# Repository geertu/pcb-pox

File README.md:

# POX - Power-Opto Extension Board (KiCad PCB)

This is a small extension board to control operation of two development boards,
e.g. on your desk, or in a board farm.  It is mainly intended for use with
BCU/2 (https://github.com/geertu/pcb-bcu2), but it can be used with any
microcontroller or single-board computer that has a compatible I2C interface.

## Features

  - Controlled over I2C,
  - Two power control and measurement channels (3.3-14V, max. 3.2A),
  - Six opto-isolators for e.g. reset, wake-up, and keypress simulation.

## Software

Software to run on BCU/2+POX is available from
https://github.com/geertu/teensy3-bcu2/tree/bcu2%2Bpox in source form.

## License

CC-BY-SA-4.0 (https://creativecommons.org/licenses/by-sa/4.0/)

## PCB and Parts

PCB and parts can be ordered at
https://aisler.net/geert/power-opto-extension/bcu2-pox (Disclaimer: I'm not
affiliated to AISLER). Note that the project at Aisler predates the change from
NTF6P02 to DMP6023LE-13.

## Bill Of Materials

  - C1, C3, C4, C7, C8: Capacitor, 100nF, SMD 0603/1608
  - C2, C5, C6, C9: Capacitor, 10µF, SMD 0805/2012, 25V
  - D1, D2: LED Green clear, SMD 0603/1608
  - D3-D8: LED Yellow clear, SMD 0603/1608
  - J1: Male 1x12 header 2.54mm
  - J2: Male 1x4 header, RM 2mm, e.g. JST B4B-PH-K
  - J3, J4: Screw type, terminal block, RM 3.5mm
  - Q1, Q3, Q4, Q6: MOSFET N-channel 60V 115mA, SOT23-3
  - Q2, Q5: MOSFET P-channel e.g. 60V 7A (DMP6023LE-13) or
				  20V 10A (NTF6P02), SOT223
  - R1, R2: Resistor, 4.7kΩ, SMD 0603/1608 (optional, I2C pull-ups)
  - R3, R8: Resistor, 47kΩ, SMD 0603/1608
  - R4, R9: Resistor, 10kΩ (when using DMP6023LE-13) or
		      47kΩ (when using NTF6P02), SMD 0603/1608
  - R5, R10: Resistor, 100kΩ, SMD 0603/1608
  - R6, R11, R13, R15, R17, R19, R21, R23: Resistor, 1kΩ, SMD 0603/1608
  - R7, R12: Resistor, 100mΩ, SMD 2512/6432, 1%, 2W
  - R14, R16, R18, R20, R22, R24: Resistor, 270Ω, SMD 0603/1608
  - U1: PFC8574, 16-SOIC (wide)
  - U2, U3: INA219xID power monitor, 8-SOIC
  - U4-U9: Opto-isolator, Mini-Flat-4, e.g. Broadcom HCPL-181-00CE

## Connector Pinouts

  - J1: Opto-isolator channels 6-11

    Pin               | Function
    ----------------- | --------
     1-11 (odd pins)  | Emitter ("negative output")
     2-12 (even pins) | Collector ("positive output")

  - J2: I2C[A]

    Pin | Function
    --- | --------
     1  | GND
     2  | +3.3V
     3  | SDA
     4  | SCL

  - J3 / J4: Power channels C & D

    Pin | Function
    --- | --------
     1  | GND
     2  | Power OUT
     3  | GND
     4  | Power IN (3.3-14V, max. 3.2A)

## Solder Jumpers

  - JP1 / JP2 / JP3: Configure the I2C address of the PCF8574 I/O expander
    (0x20 (default) to 0x27)

  - JP4: Configure the I2C addresses of the two INA219 power monitors
    (0x44/0x45 (default) or 0x40/0x41)

## Footnotes

  * [A] Pin order of the I2C connector is similar (but reversed!) to the Seeed
	Studio Grove and SparkFun Qwiic Connect systems, although the connector
	used is different (you can probably mount a real Grove connector
	instead).

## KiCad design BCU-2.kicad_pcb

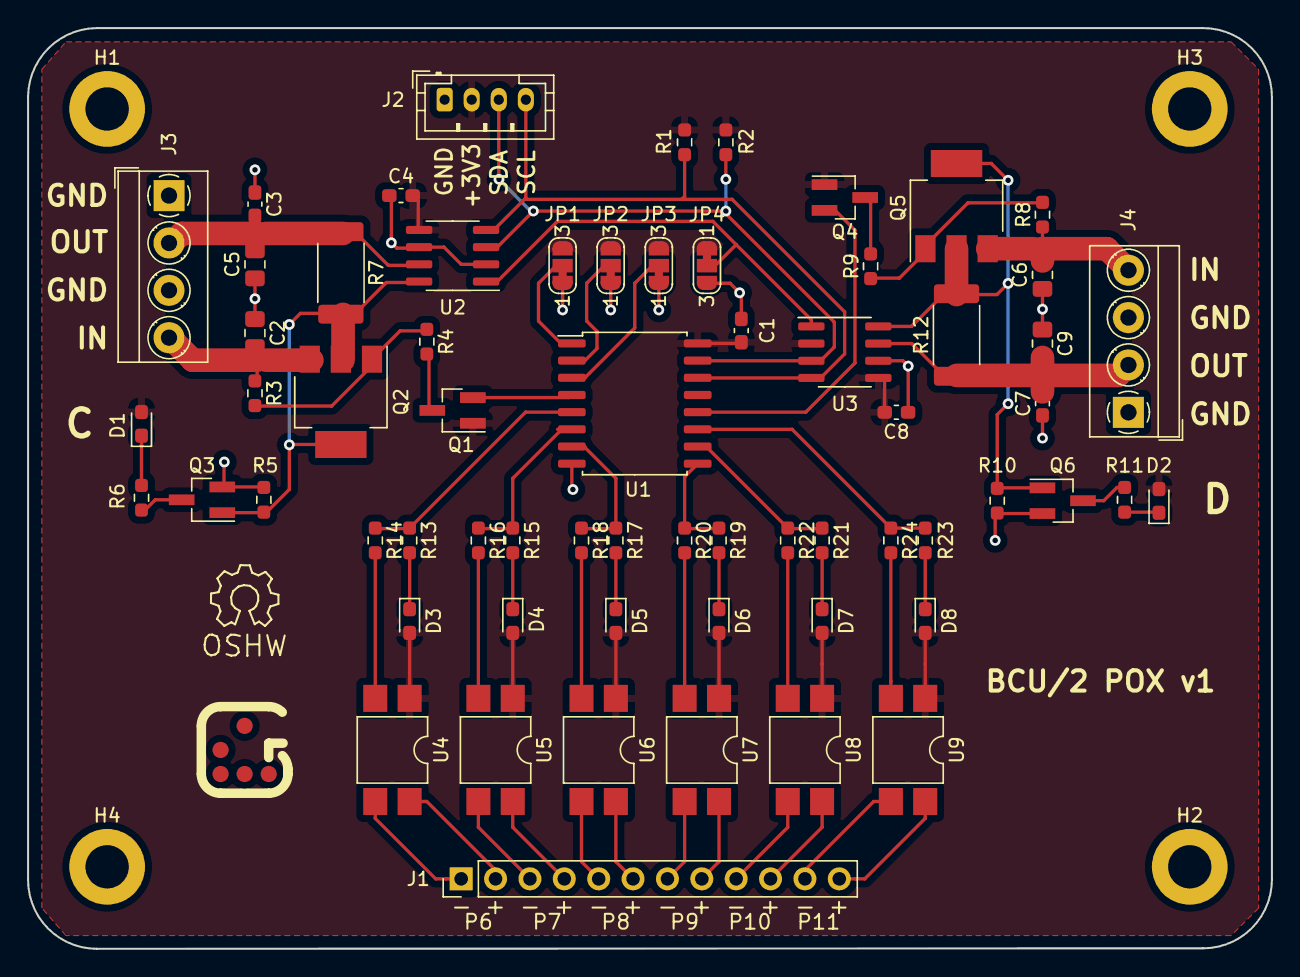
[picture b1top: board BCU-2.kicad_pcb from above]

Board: 2 copper layers, 91.9 x 68.0 mm, 70 parts (0 on the bottom side), 54 nets.

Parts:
C1, C3, C4, C7, C8: 100n; C_0603_1608Metric_Pad1.08x0.95mm_HandSolder
C2, C5, C6, C9: 10µ; C_0805_2012Metric_Pad1.18x1.45mm_HandSolder
D1, D2: Green; LED_0603_1608Metric_Pad1.05x0.95mm_HandSolder
D3, D4, D5, D6, D7, D8: Yellow; LED_0603_1608Metric_Pad1.05x0.95mm_HandSolder
Glider: Glider logo; Glider_bvba_G_Medium
H1, H2, H3, H4: MountingHole_Pad; MountingHole_3.2mm_M3_DIN965_Pad
J1: Conn_01x12_Male; PinHeader_1x12_P2.54mm_Vertical
J2: Conn_01x04_Male; JST_PH_B4B-PH-K_1x04_P2.00mm_Vertical
J3, J4: Screw_Terminal_01x04; TerminalBlock_MetzConnect_Type059_RT06304HBWC_1x04_P3.50mm_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
JP1, JP2, JP3, JP4: SolderJumper_3_Bridged12; SolderJumper-3_P1.3mm_Bridged12_RoundedPad1.0x1.5mm_NumberL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
OSHW: Symbol_OSHW-Logo_SilkScreen
Q1, Q3, Q4, Q6: 2N7002; SOT-23_Handsoldering
Q2, Q5: NTF6P02; SOT-223-3_TabPin2
R1, R2: 4K7; R_0603_1608Metric_Pad0.98x0.95mm_HandSolder
R3, R4, R8, R9: 47K; R_0603_1608Metric_Pad0.98x0.95mm_HandSolder
R5, R10: 100K; R_0603_1608Metric_Pad0.98x0.95mm_HandSolder
R6, R11, R13, R15, R17, R19, R21, R23: 1K; R_0603_1608Metric_Pad0.98x0.95mm_HandSolder
R7, R12: 0.1 1% 2W; R_2512_6332Metric_Pad1.40x3.35mm_HandSolder
R14, R16, R18, R20, R22, R24: 270; R_0603_1608Metric_Pad0.98x0.95mm_HandSolder
U1: PCF8574; SOIC-16W_7.5x10.3mm_P1.27mm
U2, U3: INA219xID; SOIC-8_3.9x4.9mm_P1.27mm
U4, U5, U6, U7, U8, U9: HCPL-181; SMDIP-4_W7.62mm

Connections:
+3V3: C1.1, C4.2, C8.2, D1.2 (A), D2.2 (A), D3.2 (A), D4.2 (A), D5.2 (A), D6.2 (A), D7.2 (A), D8.2 (A), J2.2, JP1.3 (B), JP2.3 (B), JP3.3 (B), JP4.1 (A), Q1.1 (G), Q4.1 (G), R1.1, R2.1, U1.16 (VDD), U2.5 (Vs), U3.2 (A0), U3.5 (Vs), U4.1, U5.1, U6.1, U7.1, U8.1, U9.1
/Power Channel C/A1: JP4.2 (C), U2.1 (A1), U3.1 (A1)
/Power Channel C/IN: C2.2, J3.4, Q2.3 (S), R3.1
/Power Channel C/OUT: C3.2, C5.2, J3.2, R7.1, U2.7 (Vin-)
/Power Channel D/IN: C6.2, J4.4, Q5.3 (S), R8.1
/Power Channel D/OUT: C7.2, C9.2, J4.2, R12.1, U3.7 (Vin-)
GND: C1.2, C2.1, C3.1, C4.1, C5.1, C6.1, C7.1, C8.1, C9.1, H1.1, H2.1, H3.1, H4.1, J2.1, J3.1, J3.3, J4.1, J4.3, JP1.1 (A), JP2.1 (A), JP3.1 (A), JP4.3 (B), Q3.2 (S), Q6.2 (S), R5.2, R10.2, U1.8 (VSS), U2.2 (A0), U2.6 (GND), U3.6 (GND)
unnamed: D1.1 (K), R6.1
unnamed: D2.1 (K), R11.1
unnamed: D3.1 (K), R13.2
unnamed: D4.1 (K), R15.2
unnamed: D5.1 (K), R17.2
unnamed: D6.1 (K), R19.2
unnamed: D7.1 (K), R21.2
unnamed: D8.1 (K), R23.2
unnamed: JP1.2 (C), U1.1 (A0)
unnamed: JP2.2 (C), U1.2 (A1)
unnamed: JP3.2 (C), U1.3 (A2)
unnamed: Q1.3 (D), R4.2
unnamed: Q2.1 (G), R3.2, R4.1
unnamed: Q2.2 (D), Q3.1 (G), R5.1, R7.2, U2.8 (Vin+)
unnamed: Q3.3 (D), R6.2
unnamed: Q4.3 (D), R9.2
unnamed: Q5.1 (G), R8.2, R9.1
unnamed: Q5.2 (D), Q6.1 (G), R10.1, R12.2, U3.8 (Vin+)
unnamed: Q6.3 (D), R11.2
unnamed: R14.2, U4.2
unnamed: R16.2, U5.2
unnamed: R18.2, U6.2
unnamed: R20.2, U7.2
unnamed: R22.2, U8.2
unnamed: R24.2, U9.2
P6: R13.1, R14.1, U1.5 (P1)
P6+: J1.2, U4.4
P6-: J1.1, U4.3
P7: R15.1, R16.1, U1.6 (P2)
P7+: J1.4, U5.4
P7-: J1.3, U5.3
P8: R17.1, R18.1, U1.7 (P3)
P8+: J1.6, U6.4
P8-: J1.5, U6.3
P9: R19.1, R20.1, U1.9 (P4)
P9+: J1.8, U7.4
P9-: J1.7, U7.3
P10: R21.1, R22.1, U1.10 (P5)
P10+: J1.10, U8.4
P10-: J1.9, U8.3
P11: R23.1, R24.1, U1.11 (P6)
P11+: J1.12, U9.4
P11-: J1.11, U9.3
PWRC_EN: Q1.2 (S), U1.4 (P0)
PWRD_EN: Q4.2 (S), U1.12 (P7)
SCL: J2.4, R1.2, U1.14 (SCL), U2.4 (SCL), U3.4 (SCL)
SDA: J2.3, R2.2, U1.15 (SDA), U2.3 (SDA), U3.3 (SDA)

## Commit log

2024-06-21 Update to KiCad 6
2024-06-21 PCB: Move two vias to enlarge +3V3 zone
2024-06-21 PCB: Fix clearance violation errors
    The pads on the INA219xID footprint became slightly larger in KiCad 6.
    Move a track, and refill the GND zone.
2024-06-21 PCB: Use the existing Phoenix terminal block 3D model
    instead of the non-existing MetzConnect variant.
2024-06-21 PCB: Remove unneeded stubs to fix track has unconnected end warnings
2024-06-21 PCB: Tools → Update Footprints from Library in PCB Editor
2024-06-21 PCB: Move LED labels D3-D10 to fix silkscreen overlap errors
2024-06-21 PCB: Manual fixup of resistor/capacitor/LED 3D models
2024-06-21 PCB: Connect NTF6P02 pads to drains to fix missing connection errors
    KiCad doesn't know they are connected internally.
2024-06-21 .gitignore: Update for KiCad 6
2024-06-21 Schematic: Remove LED channels
2024-06-21 Schematic: Replace Teensy 3.2 by PCF8574
2024-06-21 Schematic: Remove UART channels
2024-06-21 Rename from BCU-2 to BCU2-POX
2024-06-21 PCB: Mark OSHW and Glider logos for special handling
    The OSHW and Glider logos are not in the schematic, and to be excluded
    from the BOM. Mark them correctly, so they are not deleted by any
    future update of the PCB with changes made to schematic.
2024-06-21 Schematic: Annotate symbol references
    Fill in schematic symbol reference designators.
2024-06-21 PCB: Update layout for schematic changes
2024-06-21 Schematic: Update title and date
    Power-Opto Extension Board (POX for BCU/2)
2024-06-21 Remove the old BCU-2-cache.lib file
    It is a remnant of KiCad V5, and no longer used by KiCad 6.
2024-06-21 Schematic: Assign missing footprints
    Run footprint assignment tool.
2024-06-21 Remove the 74LV1T files
    The Power-Opto eXtension does not use 74LV1T.
2024-06-21 Replace NTF6P02 by DMP6023LE-13
    This requires updating the voltage divider providing gate voltage for
    the larger Gate Threshold (and Gate-Source) Voltage.
2024-06-21 PCB: Update size and mounting holes
2024-06-21 Schematic: Renumber Power and Opto Channels
    Renumber Power Channels to C-D, and Opto Channels to 6-11, to
    avoid ambiguity with the channel numbers on the base BCU/2.
2024-06-21 Schematic: Update footprints
    Update Capacitor, LED, and Resistor footprints to match KiCad 6.
2024-06-21 Schematic: Remove GPIO expansion connector
2024-06-21 Schematic: Add missing PWR_FLAG for GND
    As flagged by perform electrical rules check.
2024-06-21 Schematic: Re-annotate symbol references
    Fill in schematic symbol reference designators, with reset
    existing annotations.
2024-06-21 PCB: Update board name on silkscreen
    Power-Opto eXtension Rev. 1.00
2024-06-21 Schematic: Include DNP I2C pull-up resistors in BOM/board
    Else there won't be a footprint in the PCB.
2024-06-21 Schematic: Invert Power Channel Enable signal
2024-06-21 Update PCB image
    Replace the BCU/2 PCB image by the proper POX PCB image.
2024-06-22 Update README.md
    Replace the BCU/2 documentation by proper POX documentation.
